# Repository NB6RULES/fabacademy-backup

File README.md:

# 🚀 Nadec Biju – Fab Academy 2026 Portfolio

🔗 **Live Site:** https://fabacademy.org/2026/labs/kochi/students/nadec-biju/

---

## 🎬 Final Project Presentation

▶️ **[Watch the presentation video](static/presentation.mp4)** — also embedded live on the [Final Project page](https://fabacademy.org/2026/labs/kochi/students/nadec-biju/docs/final-project/)

---

## 👨‍🔧 About Me

Hey! I'm **Nadec Biju**, a Mechanical Engineering student at CUSAT (2022–2026), passionate about:

- Digital Fabrication  
- Robotics & Embedded Systems  
- CAD & Mechanical Design  

I love taking ideas from **"what if?" → "it works."**  
From off-road vehicles to fabrication projects, I focus on building real, functional systems.

---

## 🧠 Skills

- **CAD & Design:** SolidWorks, Fusion 360, Siemens NX  
- **Fabrication:** 3D Printing, Laser Cutting, CNC  
- **Programming:** Python, Arduino, ESP32  
- **Electronics:** Circuit Design, PCB Design  

---

## 🏁 Fab Academy Journey

Fab Academy is a **20-week hands-on digital fabrication program** where each week focuses on a new skill, building toward a final integrated project.

This portfolio documents my **weekly progress, builds, failures, and learnings**.

---

## 🧰 Interactive Tools — Built Along the Way

These are the highlight of this portfolio — actual working tools I built as part of weekly assignments, not just documentation.

| Tool | From | Description |
|---|---|---|
| 📏 **[Laser Kerf Calculator](https://fabacademy.org/2026/labs/kochi/students/nadec-biju/docs/assignment/week-3/laser-gauge-tool/)** | Week 3 – CNC Cutting | Calculates laser kerf compensation for precision press-fit joints |
| 🎮 **[NB6-Boy Highscores](https://fabacademy.org/2026/labs/kochi/students/nadec-biju/docs/assignment/week-4/nb6-boy/)** | Week 4 – Embedded Programming | Online highscore board for the NB6-Boy handheld game console |
| ⚙️ **[4-Bar Linkage Calculator](https://fabacademy.org/2026/labs/kochi/students/nadec-biju/docs/assignment/week-7/chair-4-bar-linkage-calculator/)** | Week 7 – CNC Milling | Solves four-bar linkage geometry for the recliner chair mechanism |
| 📐 **[Linkage Designer](https://nb6rules.github.io/Linkage-Designer/)** | Mechanism Design | Kinematic linkage design and simulation web tool |
| 👁️ **[Urumi Vision](https://nb6rules.github.io/Urumi-Vision-Web/)** | Computer Vision | Browser-based computer vision web tool |
| 📥 **[Dogbone Plugin Installer](static/files/week-20/Install-Dogbone.bat)** | Week 20 – Fusion CAM | One-click installer for an open-source Fusion 360 dogbone plugin |

---

## 📅 Weekly Assignments

### ✅ Week 01 – Principles & Practices, Project Management
Setting up the tools and systems used for the rest of the program — Git, documentation workflow, and Hugo static site setup.

### ✅ Week 02 – Computer Aided Design
Explored how designs move from 2D to 3D, the difference between raster and vector images, and 3D modeling approaches like B-Rep and F-Rep.

### ✅ Week 03 – Computer Controlled Cutting
Laser cutting and vinyl cutting, kerf testing, and a parametric press-fit construction kit. Built the **Laser Kerf Calculator** tool.

### ✅ Week 04 – Embedded Programming
Programming the XIAO ESP32-C6 for the **NB6-Boy** handheld game console — OLED display, buttons, buzzer, and NeoPixel integration with a custom game in Arduino.

### ✅ Week 05 – 3D Scanning & Printing
Additive manufacturing and reverse engineering through scanning — design rules for 3D printing, printer capability testing, and scanning workflows.

### ✅ Week 06 – Electronics Design
Circuit simulation and schematic/PCB design in KiCad for the NB6-Boy board, including custom footprint import and ERC/DRC validation.

### ✅ Week 07 – Computer Controlled Machining
Designed and fabricated a meter-scale object on a ShopBot CNC router — a Lazy Boy–style recliner chair driven by a four-bar linkage mechanism. Built the **4-Bar Linkage Calculator** tool.

### ✅ Week 08 – Electronics Production
Milled, soldered, programmed, and tested the PCB designed in Week 06 — taking it from design file to a fully functional board.

### ✅ Week 09 – Input Devices
Interfacing sensors with microcontrollers — sensor types, signal conditioning, and data acquisition.

### ✅ Week 10 – Output Devices
Designing a board around an output device — motors, drivers, and power management to make something move.

### ✅ Week 11 – Networking and Communications
Built a wireless QWERTY keyboard system — wired/wireless nodes with network addressing and local I/O.

### ✅ Week 12 – Mechanical Design (Machine Week, Part 1)
Designing mechanisms and motion systems as part of the machine-building project.

### ✅ Week 13 – Midterm Review
Final project checkpoint — turning the project idea into a concrete plan with deliverables for instructor review.

### ✅ Week 14 – Molding and Casting
Designed a mold, machined it into wax, cast a silicone negative, and produced a final resin part.

### ✅ Week 15 – Interface and Application Programming
Building user interfaces that communicate with embedded systems.

### ✅ Week 16 – System Integration
Bringing together electronics, programming, and fabrication into a cohesive functional system.

### ✅ Week 17 – Wildcard Week
Exploring a fabrication process outside the regular curriculum to support the final project. Includes the **Tool Trace** foam cutout workflow.

### ✅ Week 18 – Applications and Implications
Detailed planning of the final project and its broader impact.

### ✅ Week 19 – Invention, Intellectual Property, and Income
Figuring out IP, licensing, and how the final project design could (or couldn't) be used by others.

### 🔧 Project Development (Weeks 18–20)
The full build log for the final project — mechanical design of the tool cabinet, 5 custom PCBs (XIAO main board, XIAO sister board, drawer board, NEOBUTTON and NEOHALL-EFFECT nodes), Carvera CNC milling, foam tool cutouts, and ShopBot routing of the plywood cabinet structure. Built the **Dogbone Plugin Installer** tool along the way.

---

## 🚧 Final Project — Smart Tool Cabinet with RFID Tracking

A **Smart Tool Cabinet** that tracks tools using RFID cards for access control, with mini switches and individual microcontrollers in each tool slot to detect when tools are removed.

### What It Does
- **RFID Access Control** – Each person gets an RFID card to unlock drawers they're trained to use
- **Tool Tracking** – Mini switches in each tool slot log when tools are taken and returned
- **Automatic Alerts** – System alerts if tools aren't returned on time
- **Usage Logging** – Tracks who used what and when

### Components
**Hardware:** RFID reader & cards, mini switch sensors, solenoid locks, XIAO ESP32-C6 + CH32V003J4M6 microcontrollers, custom-fabricated enclosure
**Software:** RFID authentication, switch monitoring & data logging, alert system, mobile app (iOS and Android)

Full build log: [Project Development](https://fabacademy.org/2026/labs/kochi/students/nadec-biju/docs/assignment/project-development/) · Full writeup: [Final Project page](https://fabacademy.org/2026/labs/kochi/students/nadec-biju/docs/final-project/)

---

## 📚 What I Learned

- Designing is only **half the job** — manufacturing matters  
- Iteration and failure are critical  
- Documentation = reproducibility  
- Integration is the hardest (and most important) step  

---

## 🧑‍💼 Experience Highlights

- **Team Captain – Tarusa Motorsports**  
- **Design Lead – Hermes CUSAT**  
- **Intern – Indian Racing League / Formula 4**  
- **Founding Intern – Pre6 (AI Startup)**  

---

## 💭 Philosophy

> “Engineering isn’t just theory — it’s building things that move, fail, and finally work.”

---

## ⚡ Author

**Nadec Biju**  
Mechanical Engineer | Builder | Problem Solver

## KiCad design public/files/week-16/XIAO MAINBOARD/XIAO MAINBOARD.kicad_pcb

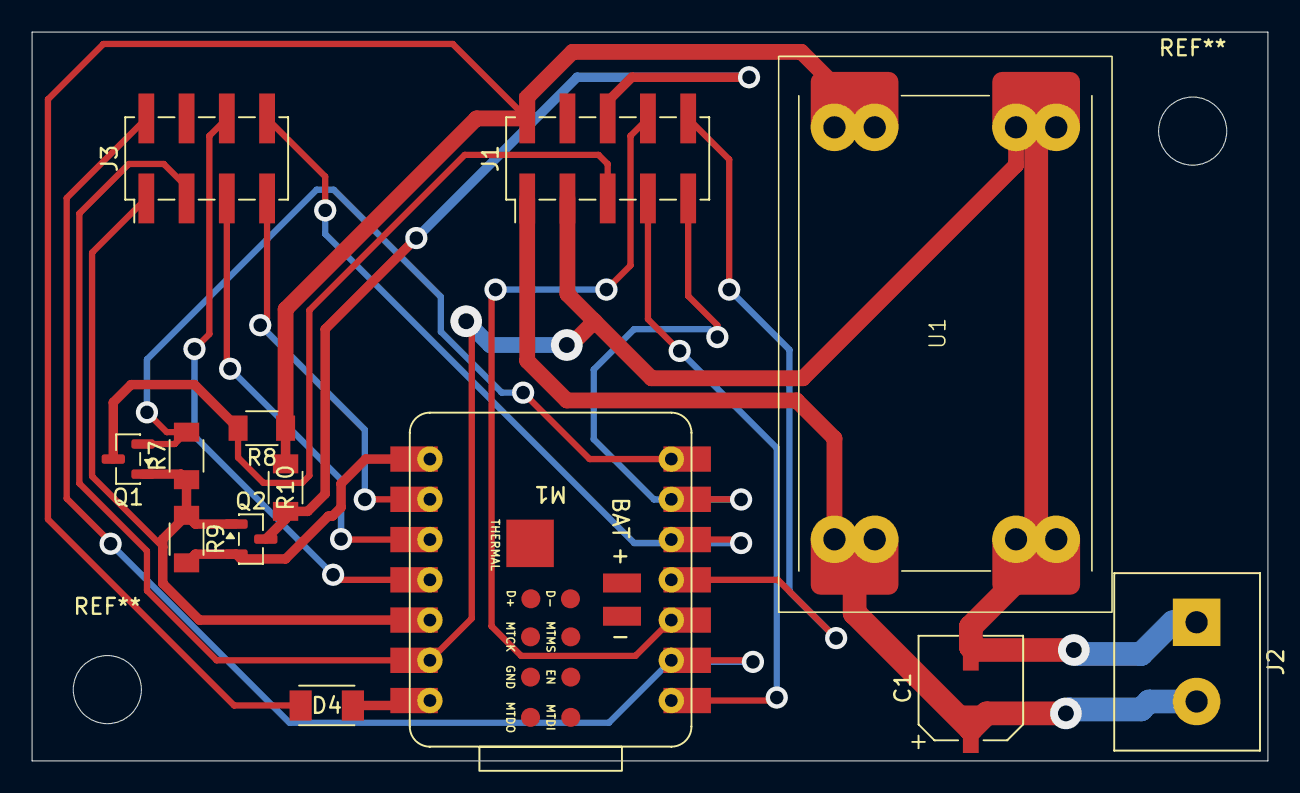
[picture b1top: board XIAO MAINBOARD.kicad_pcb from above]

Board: 2 copper layers, 78.0 x 46.0 mm, 13 parts (0 on the bottom side), 18 nets.

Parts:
C1: CP_Elec_100uF; CP_Elec_100uF_Panasonic_EEE-FN1E101UL
D4: Diode_Schottky_MiniSMA
J1: PinHeader_02x05_P2.54mm_Vertical_SMD
J2: Screw_Terminal_01x02_P5mm; TerminalBlock_OnShore_1x02_P5.00mm_Horizontal
J3: PinHeader_02x04_P2.54mm_Vertical_SMD
M1: Module_XIAO-ESP32S3; SeeedStudio_XIAO_ESP32S3
Q1, Q2: BSS138; SOT-23
R7, R8, R9, R10: 10K; R_1206
U1: Mini560_DCDC_Buck_module

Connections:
3.3v: J3.1, M1.12 (3V3), Q1.1 (G), Q2.1 (G), R7.1, R9.1
5V BUTTON DIN: J1.5, Q1.3 (D), R8.2
5V BUTTON DOUT: J1.6, Q2.3 (D), R10.2
5v: D4.2 (A), J1.2, R8.1, R10.1, U1.3 (OUT+)
12v: C1.1, J1.1, J2.2, U1.1 (IN+)
GND: C1.2, J1.3, J2.1, J3.3, M1.13 (GND), U1.2 (IN-), U1.4 (OUT-)
MISO: J3.5, M1.10 (D9)
MOSI: J3.6, M1.11 (D10)
NEOPIXEL DATA: J1.7, M1.1 (D0)
unnamed: D4.1 (K), M1.14 (5V)
RST: J3.2, M1.2 (D1)
RX - BUTTON DOUT: M1.8 (D7), Q2.2 (S), R9.2
SCK: J3.7, M1.9 (D8)
SDA: J3.8, M1.5 (D4)
Solenoid 1 Control: J1.8, M1.3 (D2)
Solenoid 2 Control: J1.10, M1.4 (D3)
Solenoid 3 Control: J1.9, M1.6 (D5)
TX - BUTTON DIN: M1.7 (D6), Q1.2 (S), R7.2

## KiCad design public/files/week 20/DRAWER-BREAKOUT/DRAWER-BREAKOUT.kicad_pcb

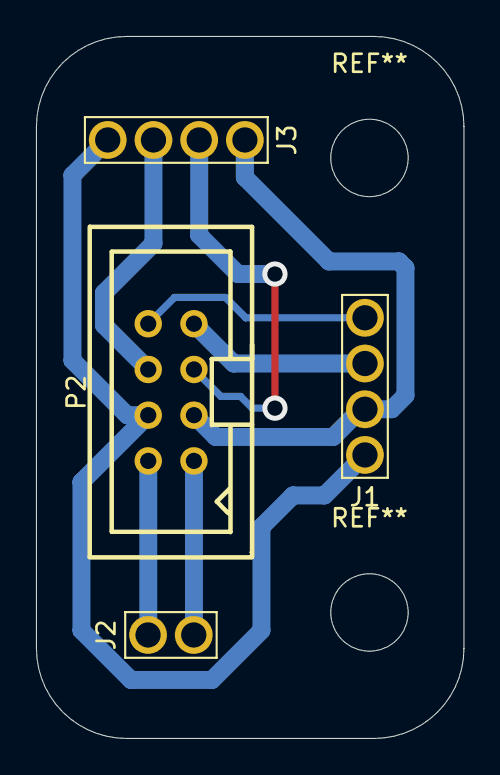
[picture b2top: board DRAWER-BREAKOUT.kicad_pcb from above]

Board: 2 copper layers, 23.8 x 39.0 mm, 4 parts (0 on the bottom side), 8 nets.

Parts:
J1, J3: PinHeader_01x04_P2.54mm_Vertical_THT_D1.4mm
J2: PinHeader_01x02_P2.54mm_Vertical_THT_D1.4mm
P2: HDR-IDC-2.54-2X4P; IDC-TH_8P-P2.54-V-R2-C4-S2.54

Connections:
5v: J1.2, J3.1, P2.3
12v: J2.2, P2.1
DRAW 1 DOUT: J3.2, P2.5
GND: J1.1, J3.4, P2.4
NEOPIXEL DATA: J1.4, P2.8
NEOPIXEL DATA OUT 1: J1.3, P2.7
Solenoid 1: J2.1, P2.2
TX - BUTTON DIN: J3.3, P2.6

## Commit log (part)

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2026-01-23 Initial commit from student template
2026-01-23 adding selfmade site to gitlab
2026-01-23 adding selfmade site to gitlab v2
2026-01-23 adding selfmade site to gitlab v3
2026-01-23 test v2
2026-01-23 Apply .gitignore
2026-01-24 Convert public from submodule to normal folder
2026-01-27 week one documentation without images
2026-01-27 edit
2026-01-27 dark mode switch
2026-01-27 agreement button open in new tab
2026-01-27 final project v1
2026-01-27 Update documentation and add planning final project page
2026-01-27 gallery images added
2026-01-27 minpor edits to gallery time
2026-01-27 rephrased basic html
2026-01-27 home page edit
2026-01-27 adding images to week1
2026-01-28 edits to hyperlinks
2026-01-28 minute week1 topic changes
2026-01-28 edits to agreement image in week1
2026-01-28 about me edits
2026-01-28 about me cusat fab edit
2026-01-28 editing the home page dp to be clickable
2026-01-28 home button added
2026-01-28 home button edit
2026-01-28 edited contact details
2026-01-29 lightmode edit
2026-02-02 second drat of week 2 including images
2026-02-02 week 2 assignment image added
2026-02-02 fusion 1.jpg added
2026-02-02 credits added aryan sv
2026-02-02 Credits added
2026-02-02 image compression added to week-2
2026-02-02 added videos and resized images
2026-02-02 Fix video paths for live server
2026-02-02 Force add video files
2026-02-02 Fix video file name case sensitivity
2026-02-02 Add favicon to website
2026-02-02 Fix favicon path and copy to static
2026-02-02 Fix favicon in correct partials folder
2026-02-02 Clean rebuild and add static files
2026-02-02 hugo regenerated reduced file size
2026-02-02 3d part complete
2026-02-02 Fix favicon - convert JPG to ICO format
2026-02-02 Fix favicon size to 64x64
2026-02-02 added 2d images
2026-02-04 final edit week 2 , added all 2d and 3d
2026-02-04 added openscad and 3dbuilder to tools used
2026-02-04 reflection updated
2026-02-04 file upload link
2026-02-04 ONSHAPE AND TINKERCAD
2026-02-04 onshape and tinkercad images
2026-02-04 fusion video compressed
2026-02-04 final project renders added to final project page
2026-02-05 WEEK 3 ADDED
2026-02-05 week 3 what i learned heading added
2026-02-05 weekly schedule added
2026-02-05 week structure from 4-18 updated
2026-02-05 v2 site theme
2026-02-05 laser gauge tool
2026-02-05 laser gauge tool EDIT
2026-02-06 student agreement fixed
2026-02-06 svg fixed
2026-02-06 laser gauge colours fixed
2026-02-07 laser gauge mac os
2026-02-07 home page edit and laser preview background and mobile view darkmode toggle
2026-02-07 mobile view changes
2026-02-09 week3 content added on 9th feb
2026-02-10 week3 consruction kit detailed
2026-02-10 kerf comb image added
2026-02-10 kerf values added
2026-02-10 adding the week files button
2026-02-10 compression gauge final
2026-02-10 changed wording in laser tool
2026-02-10 changed typo in laser tool
2026-02-10 kerf added
2026-02-10 kerf finally fixed
2026-02-11 laser statue
2026-02-11 base added to statue
2026-02-11 solidworks video compressed
2026-02-11 link fixed
2026-02-11 neil got glasses
2026-02-11 glasses buton works
2026-02-12 hero image cyberpunk
2026-02-13 blink code
2026-02-13 airbus and neopixel test
2026-02-17 week 4 documented
2026-02-17 qpad image added
2026-02-17 video compressed
2026-02-18 compressed items
2026-02-18 files compressed
2026-02-18 qpad added
2026-02-18 videos fixed
2026-02-18 leaderboard page
2026-02-18 arduino q linux
2026-02-18 video loop
2026-02-18 gameboy video
2026-02-18 qpad video added
2026-02-18 video auto play in all weeks
2026-02-18 software used updated
2026-02-18 what i learned
2026-02-18 reflection
2026-02-18 highscores button
2026-02-18 group assignment page
2026-02-18 home page week 5
2026-02-23 nueval reviwe edits 1
2026-02-23 nueval review
2026-02-24 week 5 item 1 and 2 text
2026-02-24 3d scanning text added
2026-02-24 schedule updated
2026-02-24 images added
2026-02-24 week 5 everythging except artec
2026-02-24 assigment image added
2026-02-24 goblin link added
2026-02-24 readme edit
2026-02-24 readme edit v2
2026-02-24 auto push 02-38-02-2/-
2026-02-24 auto push 02-46-02-2/-
2026-02-25 auto push 16-46-02-2/-
2026-02-25 auto push 16-51-02-2/-
2026-02-25 auto push 18-05-02-2/-
2026-02-25 auto push 19-30-02-2/-
2026-02-25 auto push 19-55-02-2/-
2026-02-25 auto push 20-04-02-2/-
2026-02-27 auto push 11-22-02-2/-
2026-03-03 auto push 15-35-02-3/-
2026-03-03 Week 6: Fix image references, add Fusion 360 embed, update component lists
2026-03-03 auto push 17-26-02-3/-
2026-03-03 auto push 17-38-02-3/-
2026-03-04 auto push 14-23-02-3/-
2026-03-04 auto push 14-56-02-3/-
2026-03-04 auto push 16-28-02-3/-
2026-03-04 auto push 16-33-02-3/-
2026-03-04 auto push 17-19-02-3/-
2026-03-04 auto push 20-22-02-3/-
2026-03-05 auto push 00-48-02-3/-
2026-03-05 auto push 04-35-02-3/-
2026-03-10 auto push 14-48-02-3/-
2026-03-10 auto push 17-46-02-3/-
2026-03-10 auto push 17-53-02-3/-
2026-03-10 auto push 17-58-02-3/-
2026-03-10 auto push 18-01-02-3/-
2026-03-10 auto push 01-07-02-3/-
2026-03-10 auto push 01-12-02-3/-
2026-03-10 auto push 01-47-02-3/-
2026-03-11 auto push 15-50-02-3/-
2026-03-11 auto push 18-34-02-3/-
2026-03-11 auto push 18-37-02-3/-
2026-03-11 auto push 19-20-02-3/-
2026-03-12 auto push 11-25-02-3/-
2026-03-18 auto push 15-33-02-3/-
2026-03-18 auto push 16-47-02-3/-
2026-03-22 auto push 14-43-02-3/-
2026-03-22 auto push 14-45-02-3/-
2026-03-23 auto backup github - 23/03/2026 17:21:01.01
2026-03-23 auto push gitlab - 23/03/2026 17:21:52.18
2026-03-24 new site
2026-03-24 auto backup github - 24/03/2026 20:37:52.69
2026-03-24 auto push gitlab - 24/03/2026 20:38:02.86
2026-03-24 new v2 site
2026-03-24 v2 site
2026-03-24 week3,4,7 added
2026-03-24 week-6 files added
2026-03-24 week-2 files added
2026-03-25 spotify
2026-03-25 letter glitch
2026-03-26 its a new week
2026-04-05 week-8 completed
2026-04-05 week-10 first commit
2026-04-06 week-11 media
2026-04-06 week -9 imgaes
2026-04-06 week 11 display state images added
2026-04-06 week-11 final ipdate
2026-04-06 week-11 phase 2
2026-04-07 phase 2 media
2026-04-29 week-14 i guess
2026-04-29 week -14 4
2026-04-29 week- 14 minor vocab changes
2026-04-30 week-15 planning
2026-05-22 week 18 first draft
2026-05-22 week 18 final
2026-05-23 week-18 images
2026-05-23 week3 updates
2026-05-23 WEEK-7 UPDATED
2026-05-23 final project schedule added
2026-05-23 week-14 pushed
2026-05-23 week-14 files added
2026-05-27 week-14 cam images added
2026-05-27 week-14 images
2026-05-27 week-15
2026-05-27 week-15 edits
2026-05-27 week-17 images added
2026-05-29 Move Project Development card to end of assignment grid and fix icon structure
2026-05-29 Replace star icon with gear icon for Project Development card
2026-05-29 week-19
2026-05-29 project deveopment added
2026-05-29 week 19 ompleted
2026-05-30 week-19 edits
2026-06-02 push before review
2026-06-02 media added to projet development
2026-06-02 carvera images added
2026-06-07 dogbone bat file added
2026-06-12 pre final project push
2026-06-12 presentation slide added
2026-06-12 v2 slide
2026-06-12 slide added and video added in final project page
2026-06-12 video added
2026-06-12 video 1080
2026-06-12 video edited to include electrnics
2026-06-12 final video i guess
2026-06-15 week-17 pushed
2026-06-15 ABOUT ME UPDATE
2026-06-15 WEEK 16 TEST
2026-06-15 WEEK-16 ADDED
2026-06-15 week-16 cover image added
2026-06-15 week -16 what i learned added
2026-06-16 week-12 update 1
2026-06-16 week -12 completed
2026-06-16 week-12 files
2026-06-16 files v2
2026-06-16 week -12 all files finally fixed and added
2026-06-17 week -10
2026-06-18 week-14 updates made
2026-06-18 output eek updated
2026-06-18 WEEK -10 IMAGES ADDED
2026-06-18 week -10 more data added
2026-06-18 week-10 coverimage added
2026-06-18 final project page completed
2026-06-19 patent added
2026-06-19 startup and invention and innovation added
2026-06-19 week-10references added
2026-06-19 week-14 updated
2026-06-23 week-7 link updated
2026-06-23 3d scanning sections added
2026-06-23 week-12 fixed
2026-06-23 week- 18 uodated
2026-06-23 week-18 uodated v2
2026-06-23 Week-10 fully completed
2026-06-23 interface week updated
2026-06-23 rfid aded to week-15
2026-06-24 week-9 pushed
2026-06-24 week-9
2026-06-25 week-6 ai use clarified
2026-06-25 week-6 ai
2026-06-25 aidisclosure electronics
2026-06-25 project tracking
2026-06-25 projet development right toc added
2026-06-25 project development part-1
2026-06-26 project development part-2
2026-06-26 PROJECT DEVELOPMENT PART-3 I GUESS
2026-06-26 project development part- 4
2026-06-26 project development part-5
2026-06-26 PROJECT DEVELOPMENT PART-6
2026-06-26 PROJECT DEVELOPMENT PART-7
2026-06-26 project development part-8
2026-06-26 project developemnt part-9
2026-06-26 Networking week updated
2026-06-26 project development part-10
2026-06-26 project developement PART-10
2026-06-26 project development part-11
2026-06-26 am i done with fab ? is this the last commit. I sure hope so
2026-06-26 file download
2026-06-26 how the downlaod button works
2026-06-26 download button story added
2026-06-27 last local eval commit
2026-06-28 macos i guess
2026-06-28 macosv2 update
2026-06-29 macos v2
2026-06-29 macos v3
2026-06-29 updates made as per the request of global evaluator
2026-06-29 final push i guess, evaluation complete and time to bid farewell i guess :(
2026-06-29 terminal made sticky
2026-06-29 robots.txt added
